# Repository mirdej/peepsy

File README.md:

# Peepsy
Simple continuity tester based on Continuity Tester by David Johnson-Davies - www.technoblogy.com

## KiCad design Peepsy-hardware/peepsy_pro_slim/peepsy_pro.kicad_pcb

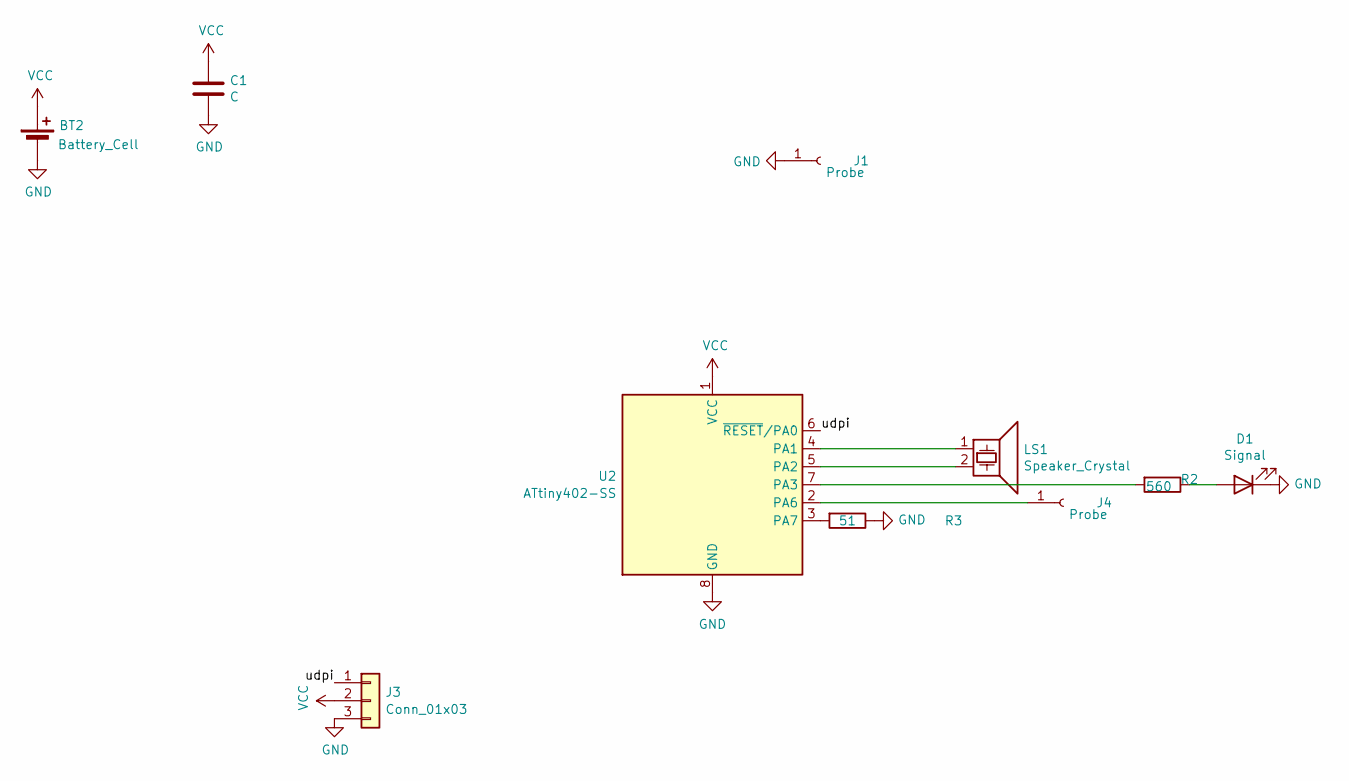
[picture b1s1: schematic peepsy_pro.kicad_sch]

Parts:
BT2: Battery_Cell; BatteryHolder_Keystone_3000_1x12mm
C1: C; C_1206_3216Metric_Pad1.42x1.75mm_HandSolder
D1: Signal; LED_1210_3225Metric_Pad1.42x2.65mm_HandSolder
J1, J4: Probe; PeepsyPad
J3: Conn_01x03; smd-3pin
LS1: Speaker_Crystal; Buzzer_CUI_CPT-9019S-SMT
R2: 560; R_0805_2012Metric_Pad1.20x1.40mm_HandSolder
R3: 51; R_0805_2012Metric_Pad1.20x1.40mm_HandSolder
U2: ATtiny402-SS; SOIC-8_3.9x4.9mm_P1.27mm

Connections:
/udpi: J3.1, U2.6 (~RESET/PA0)
GND: BT2.2 (-), C1.2, D1.1 (K), J1.1, J3.3, R3.1, U2.8 (GND)
unnamed: D1.2 (A), R2.1
unnamed: J4.1, U2.2 (PA6)
unnamed: LS1.1, U2.4 (PA1)
unnamed: LS1.2, U2.5 (PA2)
unnamed: R2.2, U2.7 (PA3)
unnamed: R3.2, U2.3 (PA7)
VCC: BT2.1 (+), C1.1, J3.2, U2.1 (VCC)

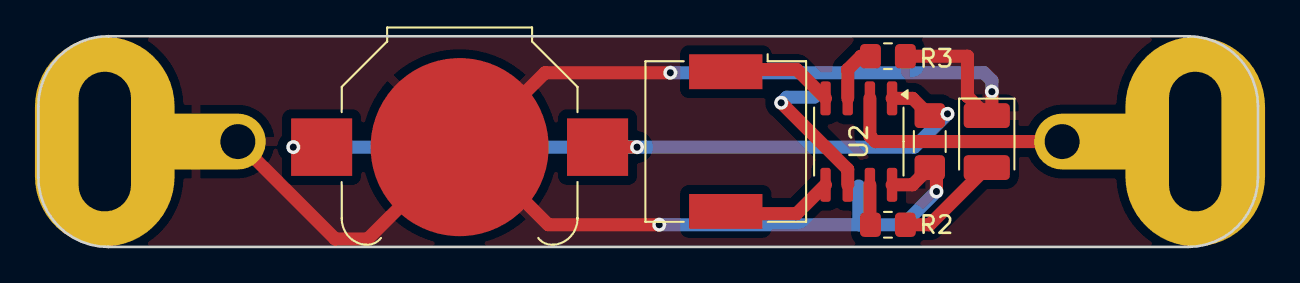
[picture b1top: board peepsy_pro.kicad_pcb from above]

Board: 2 copper layers, 69.8 x 12.1 mm, 10 parts (1 on the bottom side), 9 nets.

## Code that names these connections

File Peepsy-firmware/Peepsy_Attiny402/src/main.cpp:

/* ---------------------------------------------------------------------------------------

  PEEPSY

  by Michael Egger [ a n y m a ]

  based on Continuity Tester by David Johnson-Davies - www.technoblogy.com - 18th November 2017
  ATTINY402 @ 1 MHz (internal oscillator)

  CC BY 4.0
  Licensed under a Creative Commons Attribution 4.0 International license:
  http://creativecommons.org/licenses/by/4.0/

--------------------------------------------------------------------------------------- */

#define MILLIS_USE_TIMERB0

#include <Arduino.h>
#include "Comparator.h"

// ==============================================================================
// - Defines
// ------------------------------------------------------------------------------
#include <avr/sleep.h>
#include <avr/power.h>

const int Pin_Led = PIN_PA3;
const int Pin_Reference = PIN_PA7; // AINP0
const int Pin_Probe = PIN_PA6;     // AINN0
const int Pin_Speaker_A = PIN_PA2;
const int Pin_Speaker_B = PIN_PA1;

// ==============================================================================
// - Globals

const unsigned long Timeout = (unsigned long)20 * 1000; // twenty seconds
volatile unsigned long Time;

bool Sense;

const int freq = 1200;


// ----------------------------------------------------------------------------------------
// Pin change interrupt service routine - resets sleep timer
void wakeUp()
{
  Time = millis();
}

// ----------------------------------------------------------------------------------------
void Beep()
{
  TCA0.SINGLE.CTRLA |= TCA_SINGLE_ENABLE_bm;
  digitalWrite(Pin_Led, HIGH);
}

// ----------------------------------------------------------------------------------------
void NoBeep()
{

  TCA0.SINGLE.CTRLA &= ~TCA_SINGLE_ENABLE_bm;
  digitalWrite(Pin_Led, LOW);
}

// ==============================================================================
// - init
// ------------------------------------------------------------------------------

void setup()
{

  // Setup Analog Comparator
  Comparator.init();
  AC0.MUXCTRLA = AC_INVERT_bm;
  AC0.CTRLA = AC_ENABLE_bm;
  Comparator.start();

  // Setup Pins
  pinMode(Pin_Reference, INPUT_PULLUP);
  pinMode(Pin_Probe, INPUT_PULLUP);
  pinMode(Pin_Led, OUTPUT);
  pinMode(Pin_Speaker_A, OUTPUT);
  pinMode(Pin_Speaker_B, OUTPUT);

  //  Pin-change interrupt
  attachInterrupt(digitalPinToInterrupt(Pin_Probe), wakeUp, FALLING);
  set_sleep_mode(SLEEP_MODE_PWR_DOWN);

  // Power saving
  /* ADCSRA &= ~(1 << ADEN);									// Disable ADC to save power
  PRR = 1 << PRUSI | 1 << PRADC;							// Turn off unused clocks */

  // Setup Timer A in Frequency generation mode for beep sound
  // Inverted Signal on PINA2
  takeOverTCA0();
  TCA0.SINGLE.CMP0 = (F_CPU / (2 * freq)) + 1;
  TCA0.SINGLE.CTRLB = TCA_SINGLE_WGMODE_FRQ_gc | TCA_SINGLE_CMP1EN_bm | TCA_SINGLE_CMP2EN_bm;
  TCA0.SINGLE.CTRLA = TCA_SINGLE_CLKSEL_DIV1_gc;
  PORTA.PIN2CTRL |= PORT_INVEN_bm;

  // Start running
  Time = millis();
}

// ==============================================================================
// - LOOP
// ------------------------------------------------------------------------------
void loop()
{
  Sense = !Comparator.read();

  if (Sense)
  {
    Beep();
  }
  else

  {
    NoBeep();
  }

  // Go to sleep?
  if (millis() - Time > Timeout)
  {
    digitalWrite(Pin_Led, LOW);
    pinMode(Pin_Reference, INPUT); // Turn off pullup to save power
    sleep_enable();
    sleep_cpu();
    // Carry on here when we wake up
    pinMode(Pin_Reference, INPUT_PULLUP);
  }
}

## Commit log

2019-02-05 changed beep timer to pwm with inverted output on PB3 for more sound volume
2025-08-01 move to tiny402
2025-08-01 folder
2025-08-01 add pro version
2025-08-01 more
2025-08-01 add tiny402 version
2025-08-01 gitignor
2025-08-05 tca-doublepiezo not working
2025-08-05 working
2025-08-05 set freq
